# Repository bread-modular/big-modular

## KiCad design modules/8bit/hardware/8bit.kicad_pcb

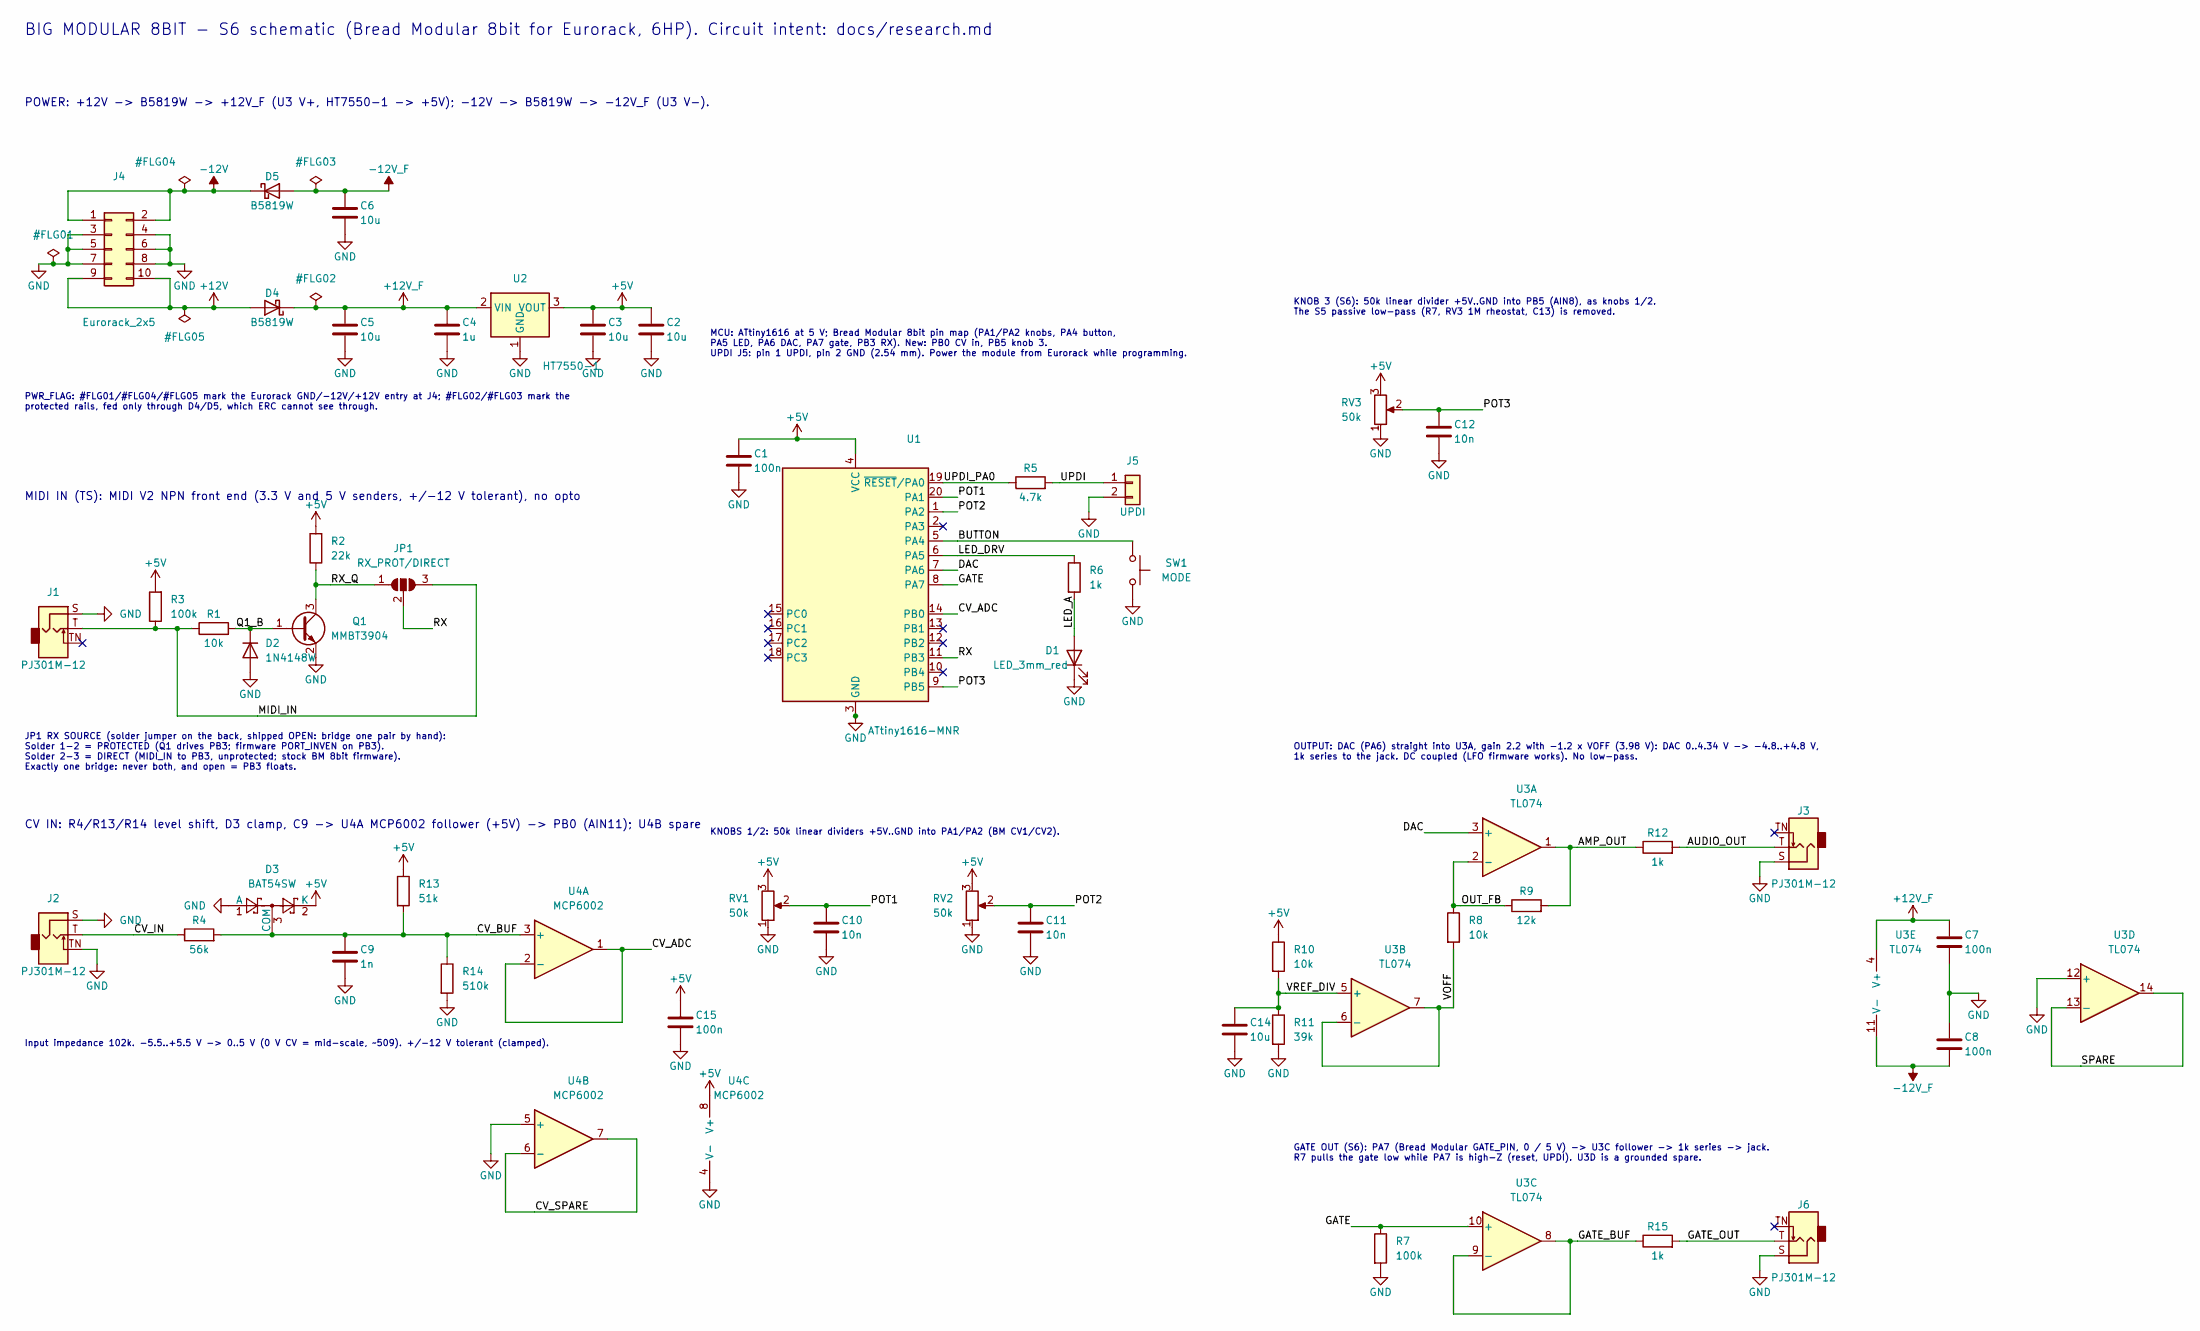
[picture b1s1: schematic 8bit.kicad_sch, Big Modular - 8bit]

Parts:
C1, C7, C8, C15: 100n; C_0603_1608Metric; Voltage 50V; MPN CC0603KRX7R9BB104; LCSC C14663
C2, C3, C5, C6, C14: 10u; C_0805_2012Metric; Voltage 25V; MPN CL21A106KAYNNNE; LCSC C15850
C4: 1u; C_0805_2012Metric; Voltage 50V; MPN CL21B105KBFNNNE; LCSC C28323
C9: 1n; C_0603_1608Metric; Voltage 50V; MPN CL10B102KB8NNNC; LCSC C1588
C10, C11, C12: 10n; C_0603_1608Metric; Voltage 50V; MPN 0603B103K500NT; LCSC C57112
D1: LED_3mm_red; LED_D3.0mm
D2: 1N4148W; D_SOD-123; MPN 1N4148W; LCSC C81598
D3: BAT54SW; SOT-323_SC-70; MPN BAT54SWT1G; LCSC C78260
D4, D5: B5819W; D_SOD-123; MPN B5819W SL; LCSC C8598
J1, J2, J3, J6: PJ301M-12; Jack_3.5mm_QingPu_WQP-PJ301M-12_Vertical
J4: Eurorack_2x5; PinHeader_2x05_P2.54mm_Vertical
J5: UPDI; PinHeader_1x02_P2.54mm_Vertical
JP1: RX_PROT/DIRECT; SolderJumper-3_P1.3mm_Open_RoundedPad1.0x1.5mm
Q1: MMBT3904; SOT-23; MPN MMBT3904(RANGE:100-300); LCSC C20526
R1, R8, R10: 10k; R_0603_1608Metric; MPN 0603WAF1002T5E; LCSC C25804
R2: 22k; R_0603_1608Metric; MPN 0603WAF2202T5E; LCSC C31850
R3, R7: 100k; R_0603_1608Metric; MPN 0603WAF1003T5E; LCSC C25803
R4: 56k; R_0603_1608Metric; MPN 0603WAF5602T5E; LCSC C23206
R5: 4.7k; R_0603_1608Metric; MPN 0603WAF4701T5E; LCSC C23162
R6: 1k; R_0603_1608Metric; MPN 0603WAF1001T5E; LCSC C21190
R9: 12k; R_0603_1608Metric; MPN 0603WAF1202T5E; LCSC C22790
R11: 39k; R_0603_1608Metric; MPN 0603WAF3902T5E; LCSC C23153
R12, R15: 1k; R_1206_3216Metric; MPN ESR18EZPF1001; LCSC C2074262
R13: 51k; R_0603_1608Metric; MPN 0603WAF5102T5E; LCSC C23196
R14: 510k; R_0603_1608Metric; MPN 0603WAF5103T5E; LCSC C23192
RV1, RV2, RV3: 50k; Potentiometer_RV09
SW1: MODE; SW_PUSH_6mm_H7.3mm; MPN 6x6x7 mm THT tact switch, 4 pins (gener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
U1: ATtiny1616-MNR; VQFN-20-1EP_3x3mm_P0.4mm_EP1.7x1.7mm; MPN ATTINY1616-MNR; LCSC C507118
U2: HT7550-1; SOT-89-3; MPN HT7550-1; LCSC C16106
U3: TL074; SOIC-14_3.9x8.7mm_P1.27mm; MPN TL074CDR; LCSC C12594
U4: MCP6002; SOIC-8_3.9x4.9mm_P1.27mm; MPN MCP6002T-I/SN; LCSC C7377

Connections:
+5V: C1.1, C2.1, C3.1, C15.1, D3.2 (K), R2.2, R3.2, R10.1, R13.1, RV1.3, RV2.3, RV3.3, U1.4 (VCC), U2.3 (VOUT), U4.8 (V+)
+12V: D4.2 (A), J4.9, J4.10
+12V_F: C4.1, C5.1, C7.1, D4.1 (K), U2.2 (VIN), U3.4 (V+)
-12V: D5.1 (K), J4.1, J4.2
-12V_F: C6.2, C8.2, D5.2 (A), U3.11 (V-)
/AMP_OUT: R9.2, R12.1, U3.1
/AUDIO_OUT: J3.T, R12.2
/BUTTON: SW1.1, U1.5 (PA4)
/CV_ADC: U1.14 (PB0), U4.1, U4.2 (-)
/CV_BUF: C9.1, D3.3 (COM), R4.2, R13.2, R14.1, U4.3 (+)
/CV_IN: J2.T, R4.1
/CV_SPARE: U4.6 (-), U4.7
/DAC: U1.7 (PA6), U3.3 (+)
/GATE: R7.1, U1.8 (PA7), U3.10 (+)
/GATE_BUF: R15.1, U3.8, U3.9 (-)
/GATE_OUT: J6.T, R15.2
/LED_A: D1.2 (A), R6.2
/LED_DRV: R6.1, U1.6 (PA5)
/MIDI_IN: J1.T, JP1.3 (B), R1.1, R3.1
/OUT_FB: R8.1, R9.1, U3.2 (-)
/POT1: C10.1, RV1.2, U1.20 (PA1)
/POT2: C11.1, RV2.2, U1.1 (PA2)
/POT3: C12.1, RV3.2, U1.9 (PB5)
/Q1_B: D2.1 (K), Q1.1 (B), R1.2
/RX: JP1.2 (C), U1.11 (PB3)
/RX_Q: JP1.1 (A), Q1.3 (C), R2.1
/SPARE: U3.13 (-), U3.14
/UPDI: J5.1, R5.2
/UPDI_PA0: R5.1, U1.19 (~RESET/PA0)
/VOFF: R8.2, U3.6 (-), U3.7
/VREF_DIV: C14.1, R10.2, R11.1, U3.5 (+)
GND: C1.2, C2.2, C3.2, C4.2, C5.2, C6.1, C7.2, C8.1, C9.2, C10.2, C11.2, C12.2, C14.2, C15.2, D1.1 (K), D2.2 (A), D3.1 (A), J1.S, J2.S, J2.TN, J3.S, J4.3, J4.4, J4.5, J4.6, J4.7, J4.8, J5.2, J6.S, Q1.2 (E), R7.2, R11.2, R14.2, RV1.1, RV2.1, RV3.1, SW1.2, U1.3 (GND), U1.21 (GND), U2.1 (GND), U3.12 (+), U4.4 (V-), U4.5 (+)

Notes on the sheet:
BIG MODULAR 8BIT - S6 schematic (Bread Modular 8bit for Eurorack, 6HP). Circuit intent: docs/research.md
JP1 RX SOURCE (solder jumper on the back, shipped OPEN: bridge one pair by hand): Solder 1-2 = PROTECTED (Q1 drives PB3; firmware PORT_INVEN on PB3). Solder 2-3 = DIRECT (MIDI_IN to PB3, unprotected; stock BM 8bit firmware). Exactly one bridge: never both, and open = PB3 floats.
Input impedance 102k. -5.5..+5.5 V -> 0..5 V (0 V CV = mid-scale, ~509). +/-12 V tolerant (clamped).
MIDI IN (TS): MIDI V2 NPN front end (3.3 V and 5 V senders, +/-12 V tolerant), no opto
MCU: ATtiny1616 at 5 V; Bread Modular 8bit pin map (PA1/PA2 knobs, PA4 button, PA5 LED, PA6 DAC, PA7 gate, PB3 RX). New: PB0 CV in, PB5 knob 3. UPDI J5: pin 1 UPDI, pin 2 GND (2.54 mm). Power the module from Eurorack while programming.
CV IN: R4/R13/R14 level shift, D3 clamp, C9 -> U4A MCP6002 follower (+5V) -> PB0 (AIN11); U4B spare
PWR_FLAG: #FLG01/#FLG04/#FLG05 mark the Eurorack GND/-12V/+12V entry at J4; #FLG02/#FLG03 mark the protected rails, fed only through D4/D5, which ERC cannot see through.
GATE OUT (S6): PA7 (Bread Modular GATE_PIN, 0 / 5 V) -> U3C follower -> 1k series -> jack. R7 pulls the gate low while PA7 is high-Z (reset, UPDI). U3D is a grounded spare.
OUTPUT: DAC (PA6) straight into U3A, gain 2.2 with -1.2 x VOFF (3.98 V): DAC 0..4.34 V -> -4.8..+4.8 V, 1k series to the jack. DC coupled (LFO firmware works). No low-pass.
POWER: +12V -> B5819W -> +12V_F (U3 V+, HT7550-1 -> +5V); -12V -> B5819W -> -12V_F (U3 V-).
KNOB 3 (S6): 50k linear divider +5V..GND into PB5 (AIN8), as knobs 1/2. The S5 passive low-pass (R7, RV3 1M rheostat, C13) is removed.
KNOBS 1/2: 50k linear dividers +5V..GND into PA1/PA2 (BM CV1/CV2).

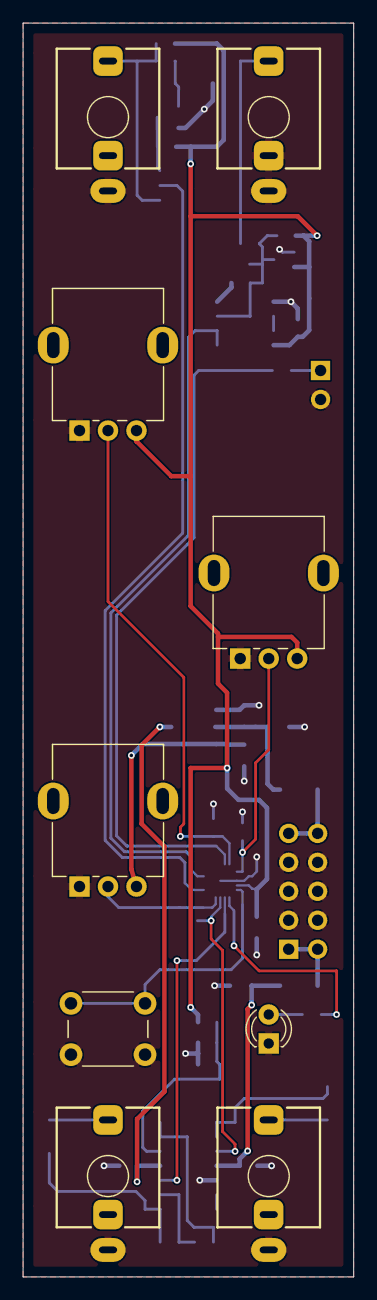
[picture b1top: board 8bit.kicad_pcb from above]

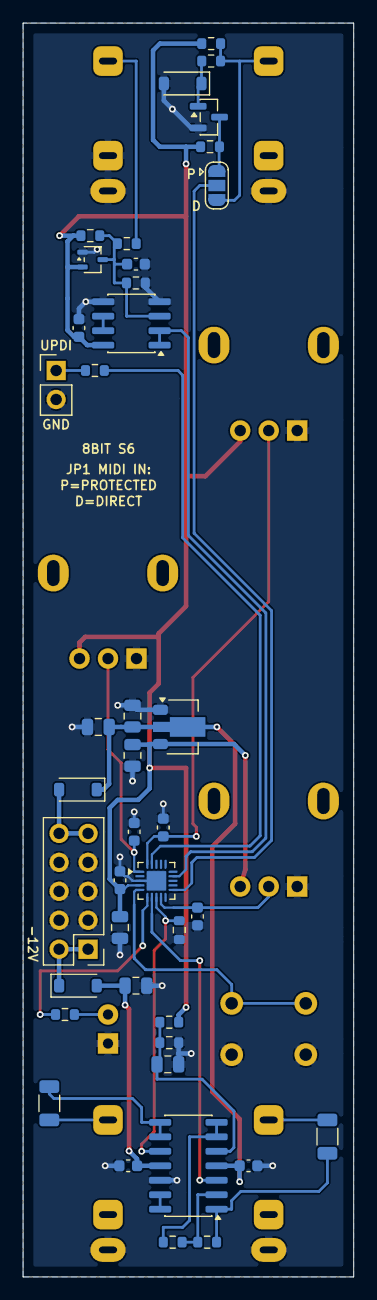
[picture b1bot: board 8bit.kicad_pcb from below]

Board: 2 copper layers, 29.0 x 110.0 mm, 50 parts (41 on the bottom side), 32 nets.

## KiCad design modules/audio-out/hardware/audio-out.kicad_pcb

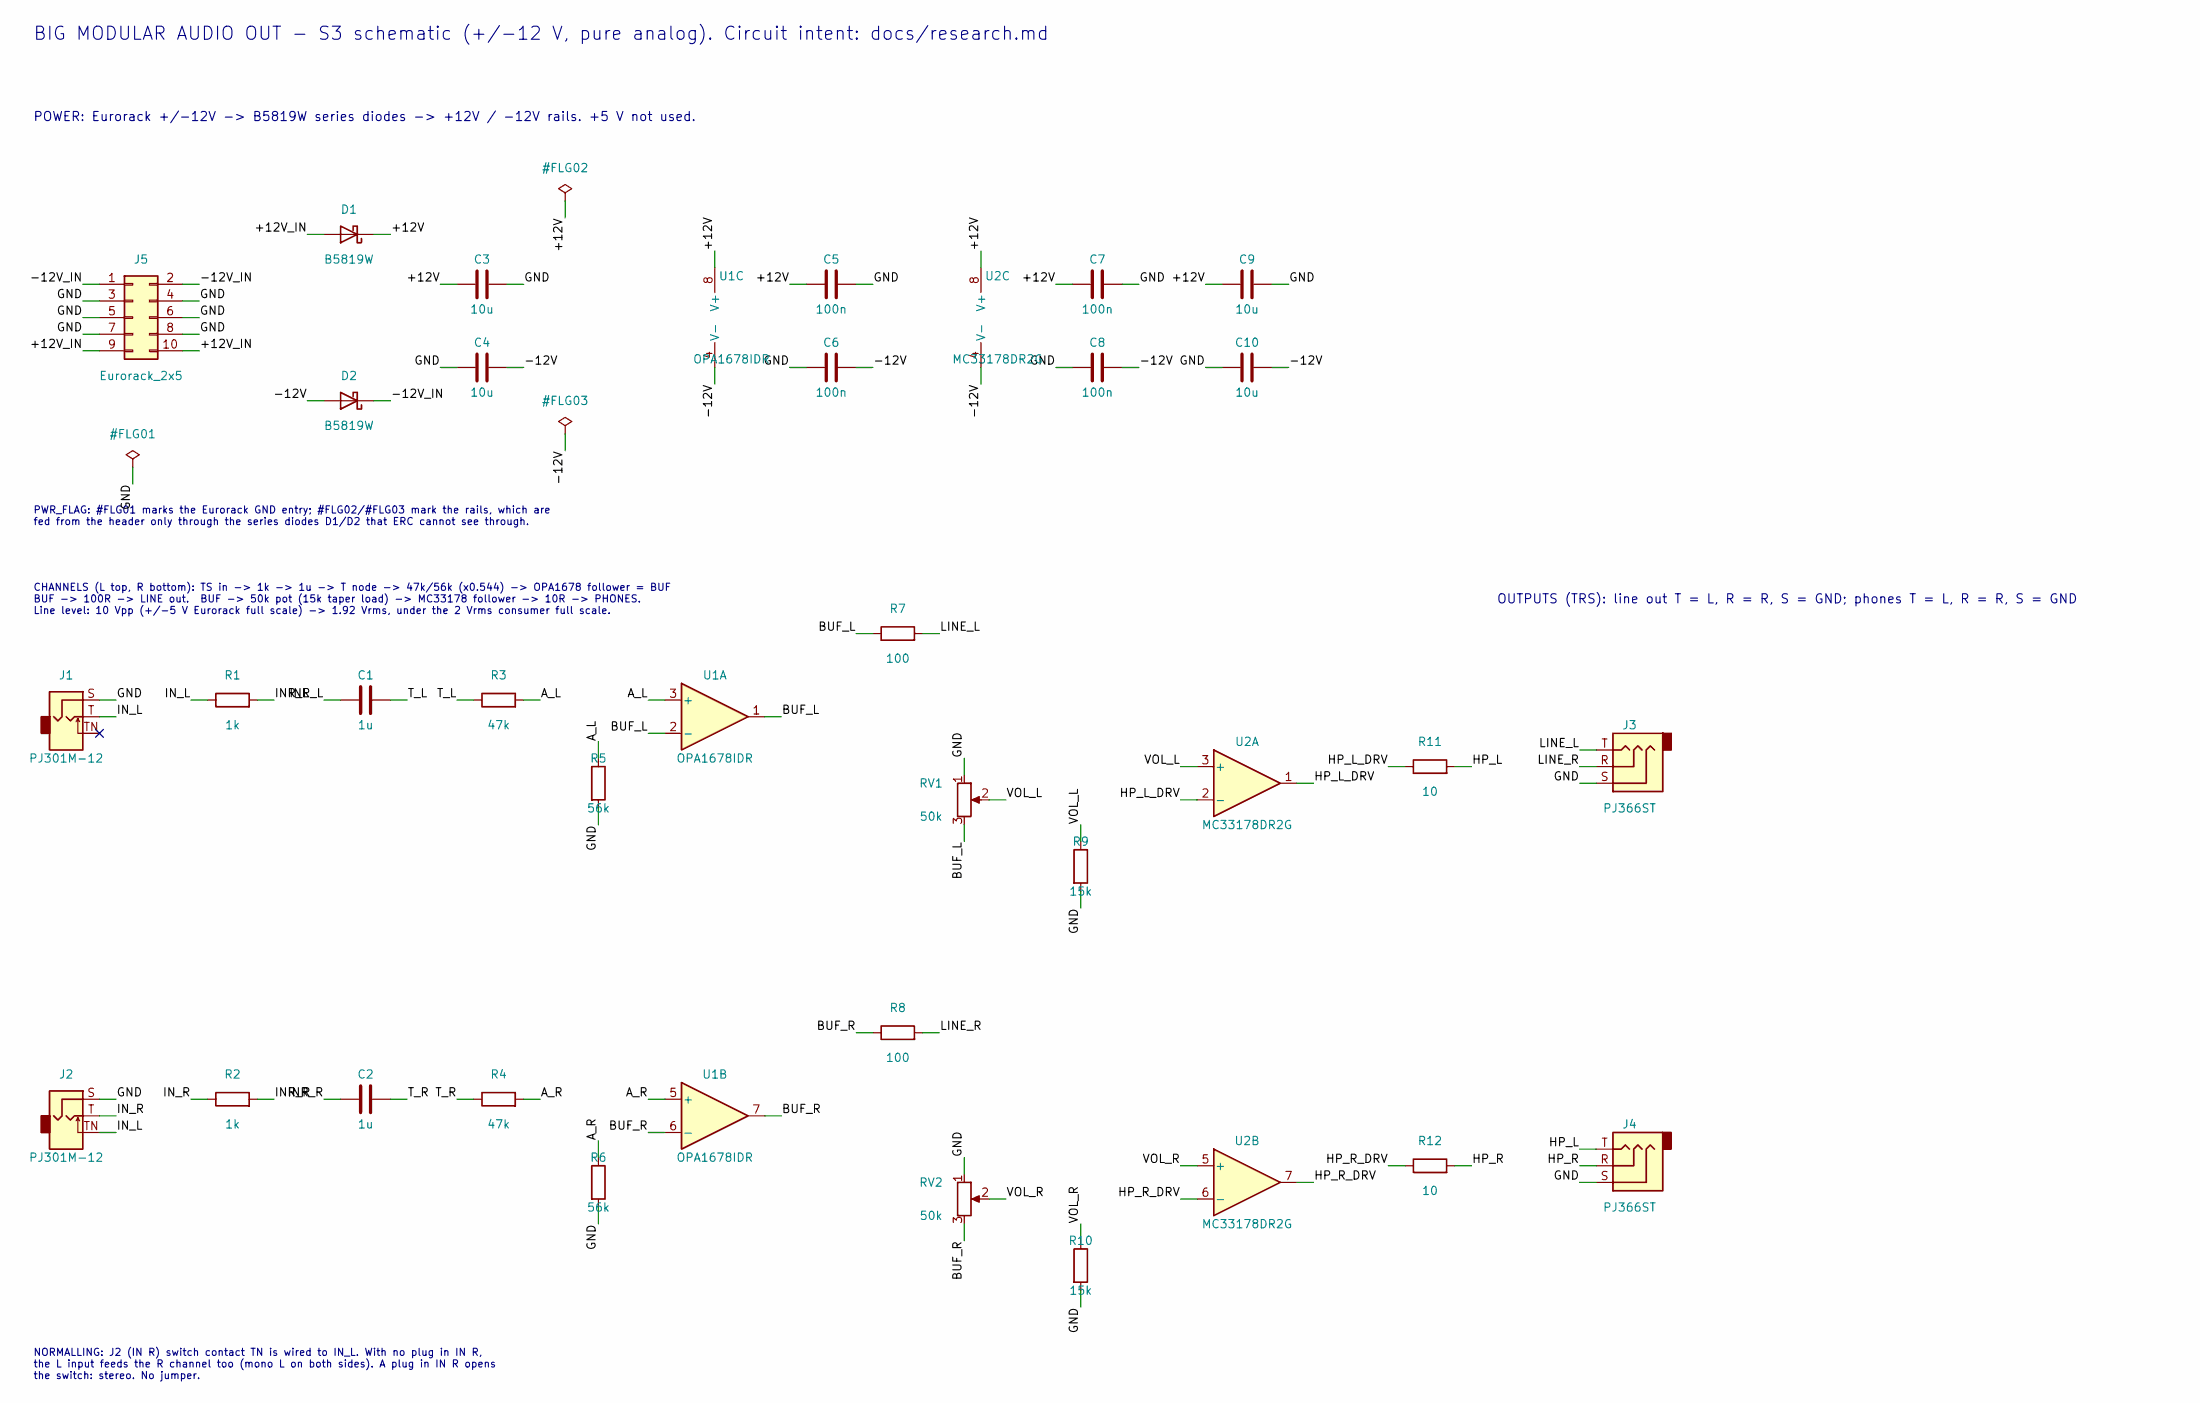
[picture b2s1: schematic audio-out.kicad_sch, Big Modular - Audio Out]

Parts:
C1, C2: 1u; C_0805_2012Metric; Voltage 50V; MPN CL21B105KBFNNNE; LCSC C28323
C3, C4, C9, C10: 10u; C_0805_2012Metric; Voltage 25V; MPN CL21A106KAYNNNE; LCSC C15850
C5, C6, C7, C8: 100n; C_0603_1608Metric; Voltage 50V; MPN CC0603KRX7R9BB104; LCSC C14663
D1, D2: B5819W; D_SOD-123; MPN B5819W SL; LCSC C8598
J1, J2: PJ301M-12; Jack_3.5mm_QingPu_WQP-PJ301M-12_Vertical
J3, J4: PJ366ST; Jack_3.5mm_QingPu_WQP-PJ366ST_Vertical
J5: Eurorack_2x5; PinHeader_2x05_P2.54mm_Vertical
R1, R2: 1k; R_0603_1608Metric; MPN 0603WAF1001T5E; LCSC C21190
R3, R4: 47k; R_0603_1608Metric; MPN 0603WAF4702T5E; LCSC C25819
R5, R6: 56k; R_0603_1608Metric; MPN 0603WAF5602T5E; LCSC C23206
R7, R8: 100; R_0603_1608Metric; MPN 0603WAF1000T5E; LCSC C22775
R9, R10: 15k; R_0603_1608Metric; MPN 0603WAF1502T5E; LCSC C22809
R11, R12: 10; R_1206_3216Metric; MPN 1206W4F100JT5E; LCSC C17903
RV1, RV2: 50k; Potentiometer_RV09
U1: OPA1678IDR; SOIC-8_3.9x4.9mm_P1.27mm; MPN OPA1678IDR; LCSC C192421
U2: MC33178DR2G; SOIC-8_3.9x4.9mm_P1.27mm; MPN MC33178DR2G; LCSC C39113

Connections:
/+12V: C3.1, C5.1, C7.1, C9.1, D1.1 (K), U1.8 (V+), U2.8 (V+)
/+12V_IN: D1.2 (A), J5.9, J5.10
/-12V: C4.2, C6.2, C8.2, C10.2, D2.2 (A), U1.4 (V-), U2.4 (V-)
/-12V_IN: D2.1 (K), J5.1, J5.2
/A_L: R3.2, R5.1, U1.3 (+)
/A_R: R4.2, R6.1, U1.5 (+)
/BUF_L: R7.1, RV1.3, U1.1, U1.2 (-)
/BUF_R: R8.1, RV2.3, U1.6 (-), U1.7
/GND: C3.2, C4.1, C5.2, C6.1, C7.2, C8.1, C9.2, C10.1, J1.S, J2.S, J3.S, J4.S, J5.3, J5.4, J5.5, J5.6, J5.7, J5.8, R5.2, R6.2, R9.2, R10.2, RV1.1, RV2.1
/HP_L: J4.T, R11.2
/HP_L_DRV: R11.1, U2.1, U2.2 (-)
/HP_R: J4.R, R12.2
/HP_R_DRV: R12.1, U2.6 (-), U2.7
/INR_L: C1.1, R1.2
/INR_R: C2.1, R2.2
/IN_L: J1.T, J2.TN, R1.1
/IN_R: J2.T, R2.1
/LINE_L: J3.T, R7.2
/LINE_R: J3.R, R8.2
/T_L: C1.2, R3.1
/T_R: C2.2, R4.1
/VOL_L: R9.1, RV1.2, U2.3 (+)
/VOL_R: R10.1, RV2.2, U2.5 (+)

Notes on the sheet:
BIG MODULAR AUDIO OUT - S3 schematic (+/-12 V, pure analog). Circuit intent: docs/research.md
PWR_FLAG: #FLG01 marks the Eurorack GND entry; #FLG02/#FLG03 mark the rails, which are fed from the header only through the series diodes D1/D2 that ERC cannot see through.
CHANNELS (L top, R bottom): TS in -> 1k -> 1u -> T node -> 47k/56k (x0.544) -> OPA1678 follower = BUF BUF -> 100R -> LINE out. BUF -> 50k pot (15k taper load) -> MC33178 follower -> 10R -> PHONES. Line level: 10 Vpp (+/-5 V Eurorack full scale) -> 1.92 Vrms, under the 2 Vrms consumer full scale.
OUTPUTS (TRS): line out T = L, R = R, S = GND; phones T = L, R = R, S = GND
POWER: Eurorack +/-12V -> B5819W series diodes -> +12V / -12V rails. +5 V not used.
NORMALLING: J2 (IN R) switch contact TN is wired to IN_L. With no plug in IN R, the L input feeds the R channel too (mono L on both sides). A plug in IN R opens the switch: stereo. No jumper.

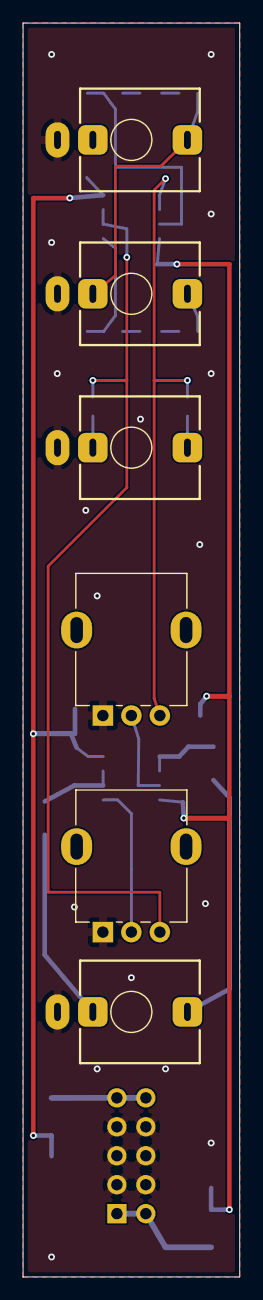
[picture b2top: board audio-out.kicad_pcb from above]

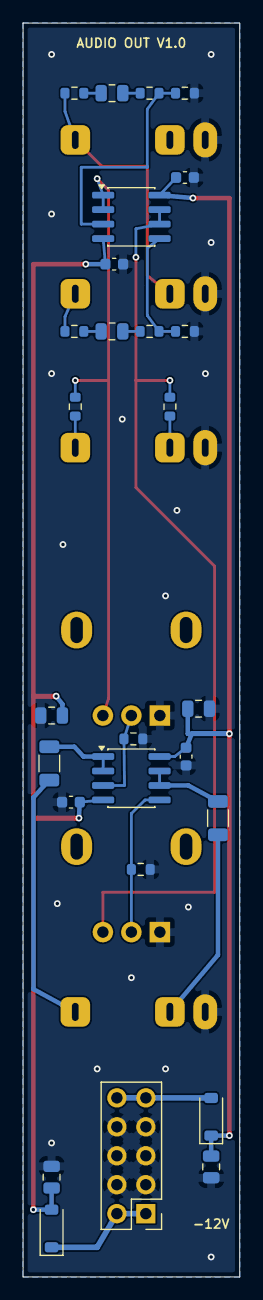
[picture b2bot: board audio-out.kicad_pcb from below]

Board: 2 copper layers, 19.0 x 110.0 mm, 33 parts (27 on the bottom side), 23 nets.
